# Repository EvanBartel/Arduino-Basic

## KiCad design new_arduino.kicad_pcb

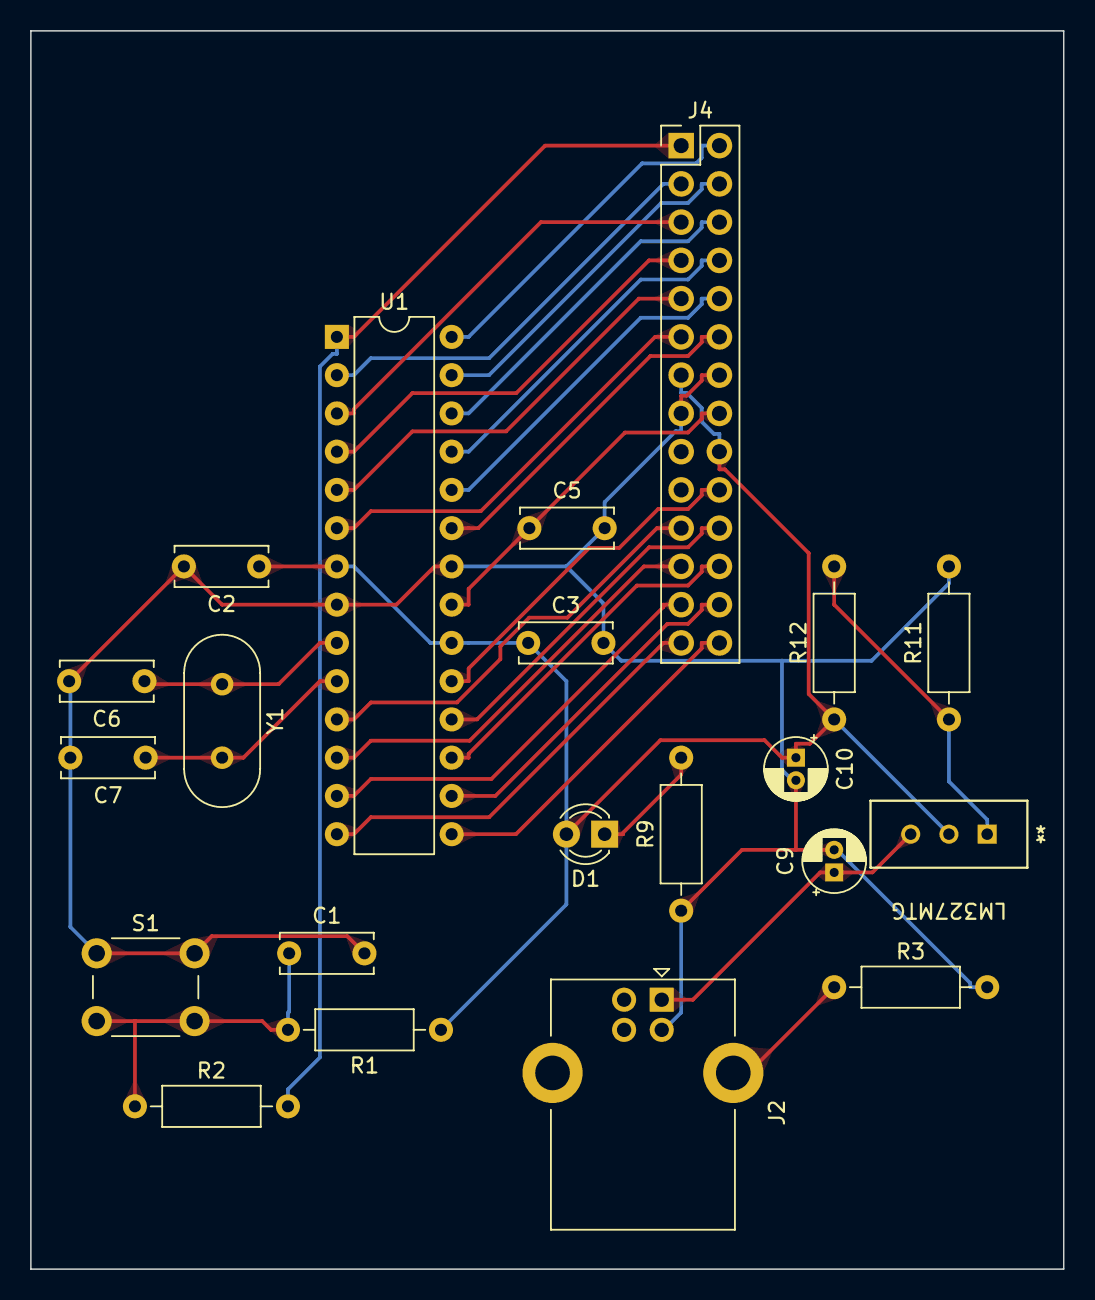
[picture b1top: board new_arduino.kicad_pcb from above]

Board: 2 copper layers, 68.6 x 82.2 mm, 21 parts (0 on the bottom side), 10 nets.

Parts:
C1, C2, C3, C5, C6, C7: C_Disc_D6.0mm_W2.5mm_P5.00mm
C9, C10: CP_Radial_D4.0mm_P1.50mm
D1: LED_D3.0mm
J2: USB_B_Lumberg_2411_02_Horizontal
J4: PinHeader_2x14_P2.54mm_Vertical
LM327MTG: LM317MTG; TO220-3_ONS
R1: 10k; R_Axial_DIN0207_L6.3mm_D2.5mm_P10.16mm_Horizontal
R2, R9, R11: 1000; R_Axial_DIN0207_L6.3mm_D2.5mm_P10.16mm_Horizontal
R3: 1M; R_Axial_DIN0207_L6.3mm_D2.5mm_P10.16mm_Horizontal
R12: 330; R_Axial_DIN0207_L6.3mm_D2.5mm_P10.16mm_Horizontal
S1: SW_PUSH_6mm
U1: ATmega328P-P; DIP-28_W7.62mm
Y1: Crystal_HC49-4H_Vertical

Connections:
GND: C1.2, C2.2, C3.2, C5.2, C6.2, C7.2, C9.2, C10.2, J2.4, J4.8, J4.22, R3.2, R9.1, R11.2, S1.1, U1.8 (GND), U1.22 (GND)
LEDneg: D1.1, R9.2
unnamed: LM327MTG.1 (ADJUST), R11.1, R12.2
OSC1: C6.1, U1.9 (XTAL1/PB6), Y1.1
OSC2: C7.1, U1.10 (XTAL2/PB7), Y1.2
Power: C2.1, C3.1, C10.1, D1.2, J4.7, J4.20, LM327MTG.2 (VOUT), R1.1, R12.1, U1.7 (VCC), U1.20 (AVCC)
RESET: J4.1, R2.2, U1.1 (~RESET/PC6)
Reset_middle: C1.1, R1.2, R2.1, S1.2
Shield: J2.5, R3.1
Vin: C9.1, J2.1, LM327MTG.3 (VIN)
